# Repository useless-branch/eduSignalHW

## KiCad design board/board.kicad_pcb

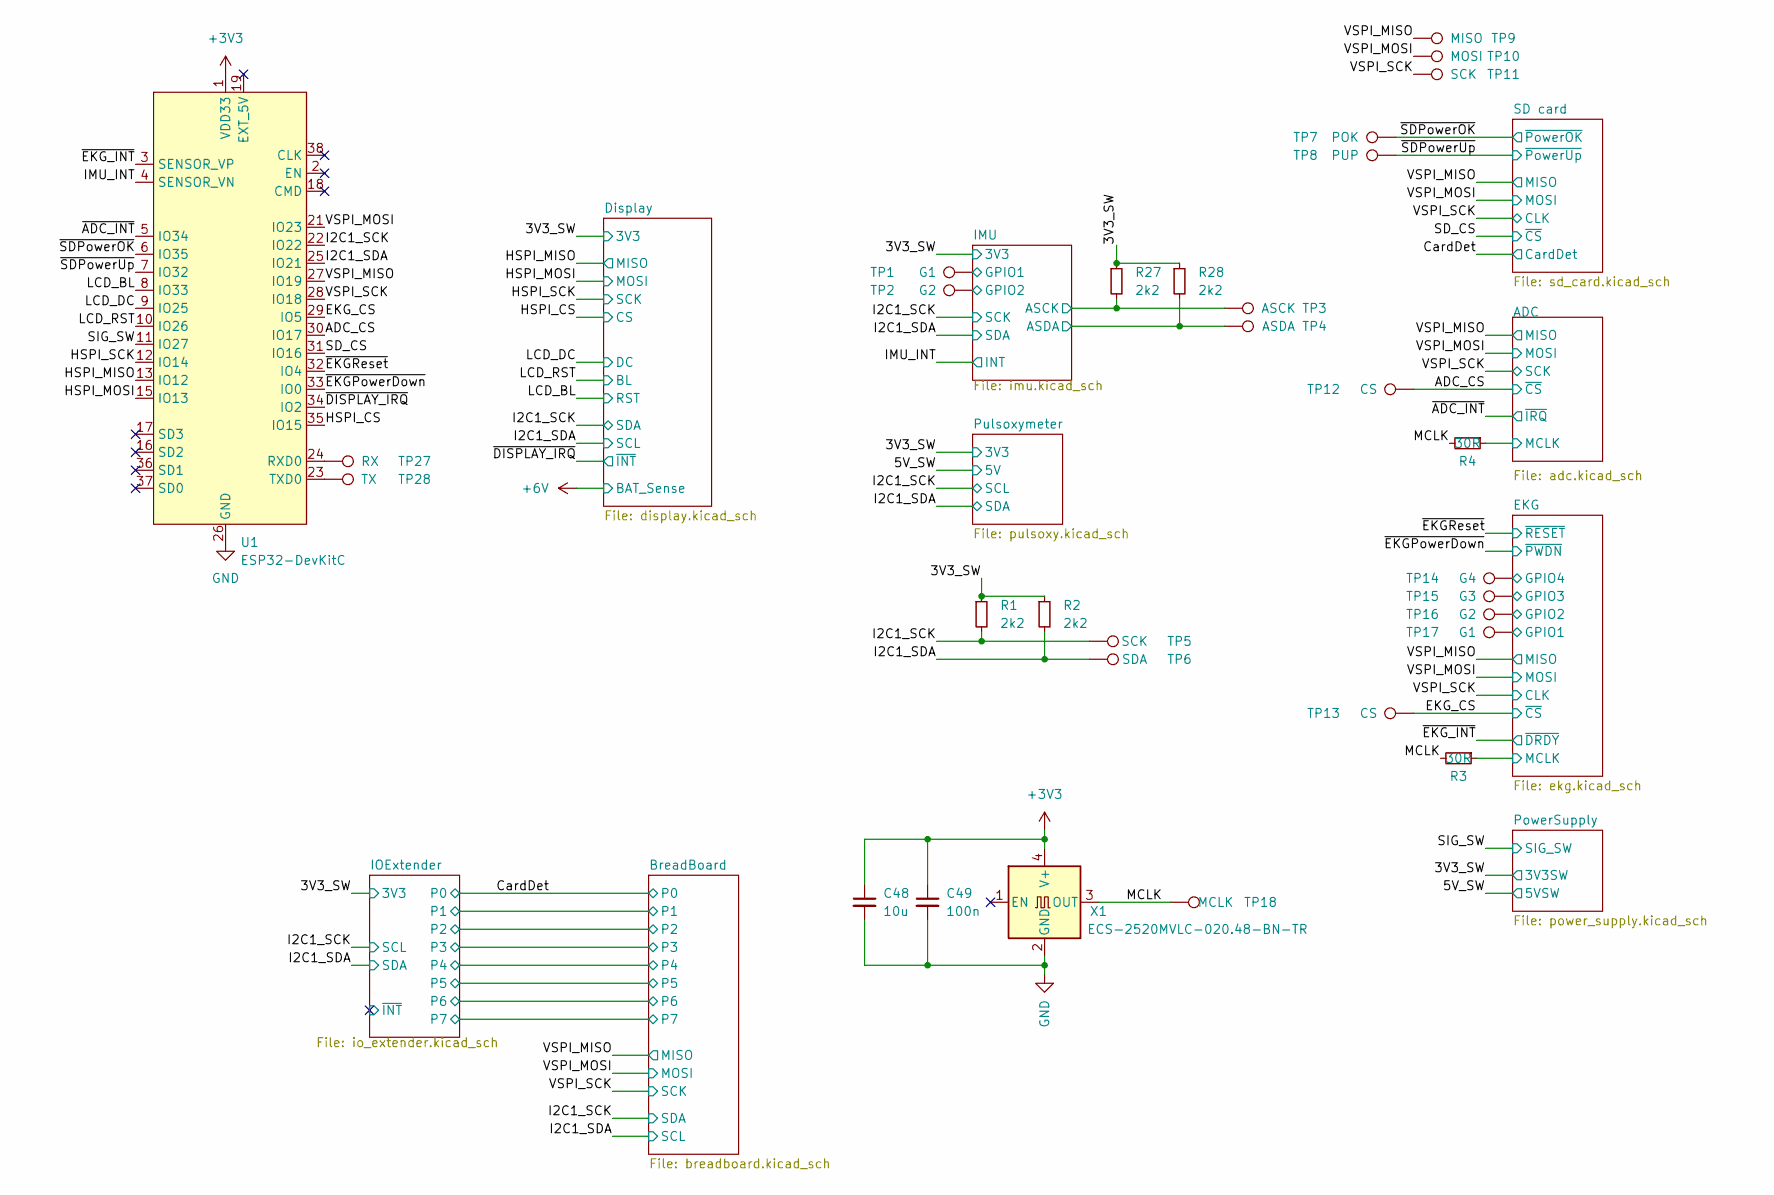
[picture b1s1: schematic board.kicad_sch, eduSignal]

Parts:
C48: 10u; C_0603_1608Metric
C49: 100n; C_0402_1005Metric
R1, R2, R27, R28: 2k2; R_0402_1005Metric
R3, R4: 30R; R_0402_1005Metric
TP1, TP17: G1; TestPoint_Pad_D1.0mm
TP2, TP16: G2; TestPoint_Pad_D1.0mm
TP3: ASCK; TestPoint_Pad_D1.0mm
TP4: ASDA; TestPoint_Pad_D1.0mm
TP5, TP11: SCK; TestPoint_Pad_D1.0mm
TP6: SDA; TestPoint_Pad_D1.0mm
TP7: POK; TestPoint_Pad_D1.0mm
TP8: PUP; TestPoint_Pad_D1.0mm
TP9: MISO; TestPoint_Pad_D1.0mm
TP10: MOSI; TestPoint_Pad_D1.0mm
TP12, TP13: CS; TestPoint_Pad_D1.0mm
TP14: G4; TestPoint_Pad_D1.0mm
TP15: G3; TestPoint_Pad_D1.0mm
TP18: MCLK; TestPoint_Pad_D1.0mm
TP27: RX; TestPoint_Pad_D1.0mm
TP28: TX; TestPoint_Pad_D1.0mm
U1: ESP32-DevKitC
X1: ECS-2520MVLC-020.48-BN-TR; Oscillator_SMD_EuroQuartz_XO32-4Pin_3.2x2.5mm

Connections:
+3V3: C48.1, C49.1, U1.1 (VDD33), X1.4 (V+); also elsewhere on the board
/3V3_SW: R1.1, R2.1, R27.1, R28.1; also elsewhere on the board
/ADC/MCLK: R4.1; also elsewhere on the board
/ADC_CS: TP12.1, U1.30 (IO17); also elsewhere on the board
/EKG/GPIO1: TP17.1; also elsewhere on the board
/EKG/GPIO2: TP16.1; also elsewhere on the board
/EKG/GPIO3: TP15.1; also elsewhere on the board
/EKG/GPIO4: TP14.1; also elsewhere on the board
/EKG/MCLK: R3.1; also elsewhere on the board
/EKG_CS: TP13.1, U1.29 (IO5); also elsewhere on the board
/HSPI_CS: U1.35 (IO15); also elsewhere on the board
/HSPI_MISO: U1.13 (IO12); also elsewhere on the board
/HSPI_MOSI: U1.15 (IO13); also elsewhere on the board
/HSPI_SCK: U1.12 (IO14); also elsewhere on the board
/I2C1_SCK: R1.2, TP5.1, U1.22 (IO22); also elsewhere on the board
/I2C1_SDA: R2.2, TP6.1, U1.25 (IO21); also elsewhere on the board
/IMU/ASCK: R27.2, TP3.1; also elsewhere on the board
/IMU/ASDA: R28.2, TP4.1; also elsewhere on the board
/IMU/GPIO1: TP1.1; also elsewhere on the board
/IMU/GPIO2: TP2.1; also elsewhere on the board
/IMU_INT: U1.4 (SENSOR_VN); also elsewhere on the board
/LCD_BL: U1.8 (IO33); also elsewhere on the board
/LCD_DC: U1.9 (IO25); also elsewhere on the board
/LCD_RST: U1.10 (IO26); also elsewhere on the board
/MCLK: R3.2, R4.2, TP18.1, X1.3 (OUT)
/SD_CS: U1.31 (IO16); also elsewhere on the board
/SIG_SW: U1.11 (IO27); also elsewhere on the board
/VSPI_MISO: TP9.1, U1.27 (IO19); also elsewhere on the board
/VSPI_MOSI: TP10.1, U1.21 (IO23); also elsewhere on the board
/VSPI_SCK: TP11.1, U1.28 (IO18); also elsewhere on the board
/~ADC_INT: U1.5 (IO34); also elsewhere on the board
/~DISPLAY_IRQ: U1.34 (IO2); also elsewhere on the board
/~EKGPowerDown: U1.33 (IO0); also elsewhere on the board
/~EKGReset: U1.32 (IO4); also elsewhere on the board
/~EKG_INT: U1.3 (SENSOR_VP); also elsewhere on the board
/~SDPowerOK: TP7.1, U1.6 (IO35); also elsewhere on the board
/~SDPowerUp: TP8.1, U1.7 (IO32); also elsewhere on the board
unnamed: TP27.1, U1.24 (RXD0)
unnamed: TP28.1, U1.23 (TXD0)

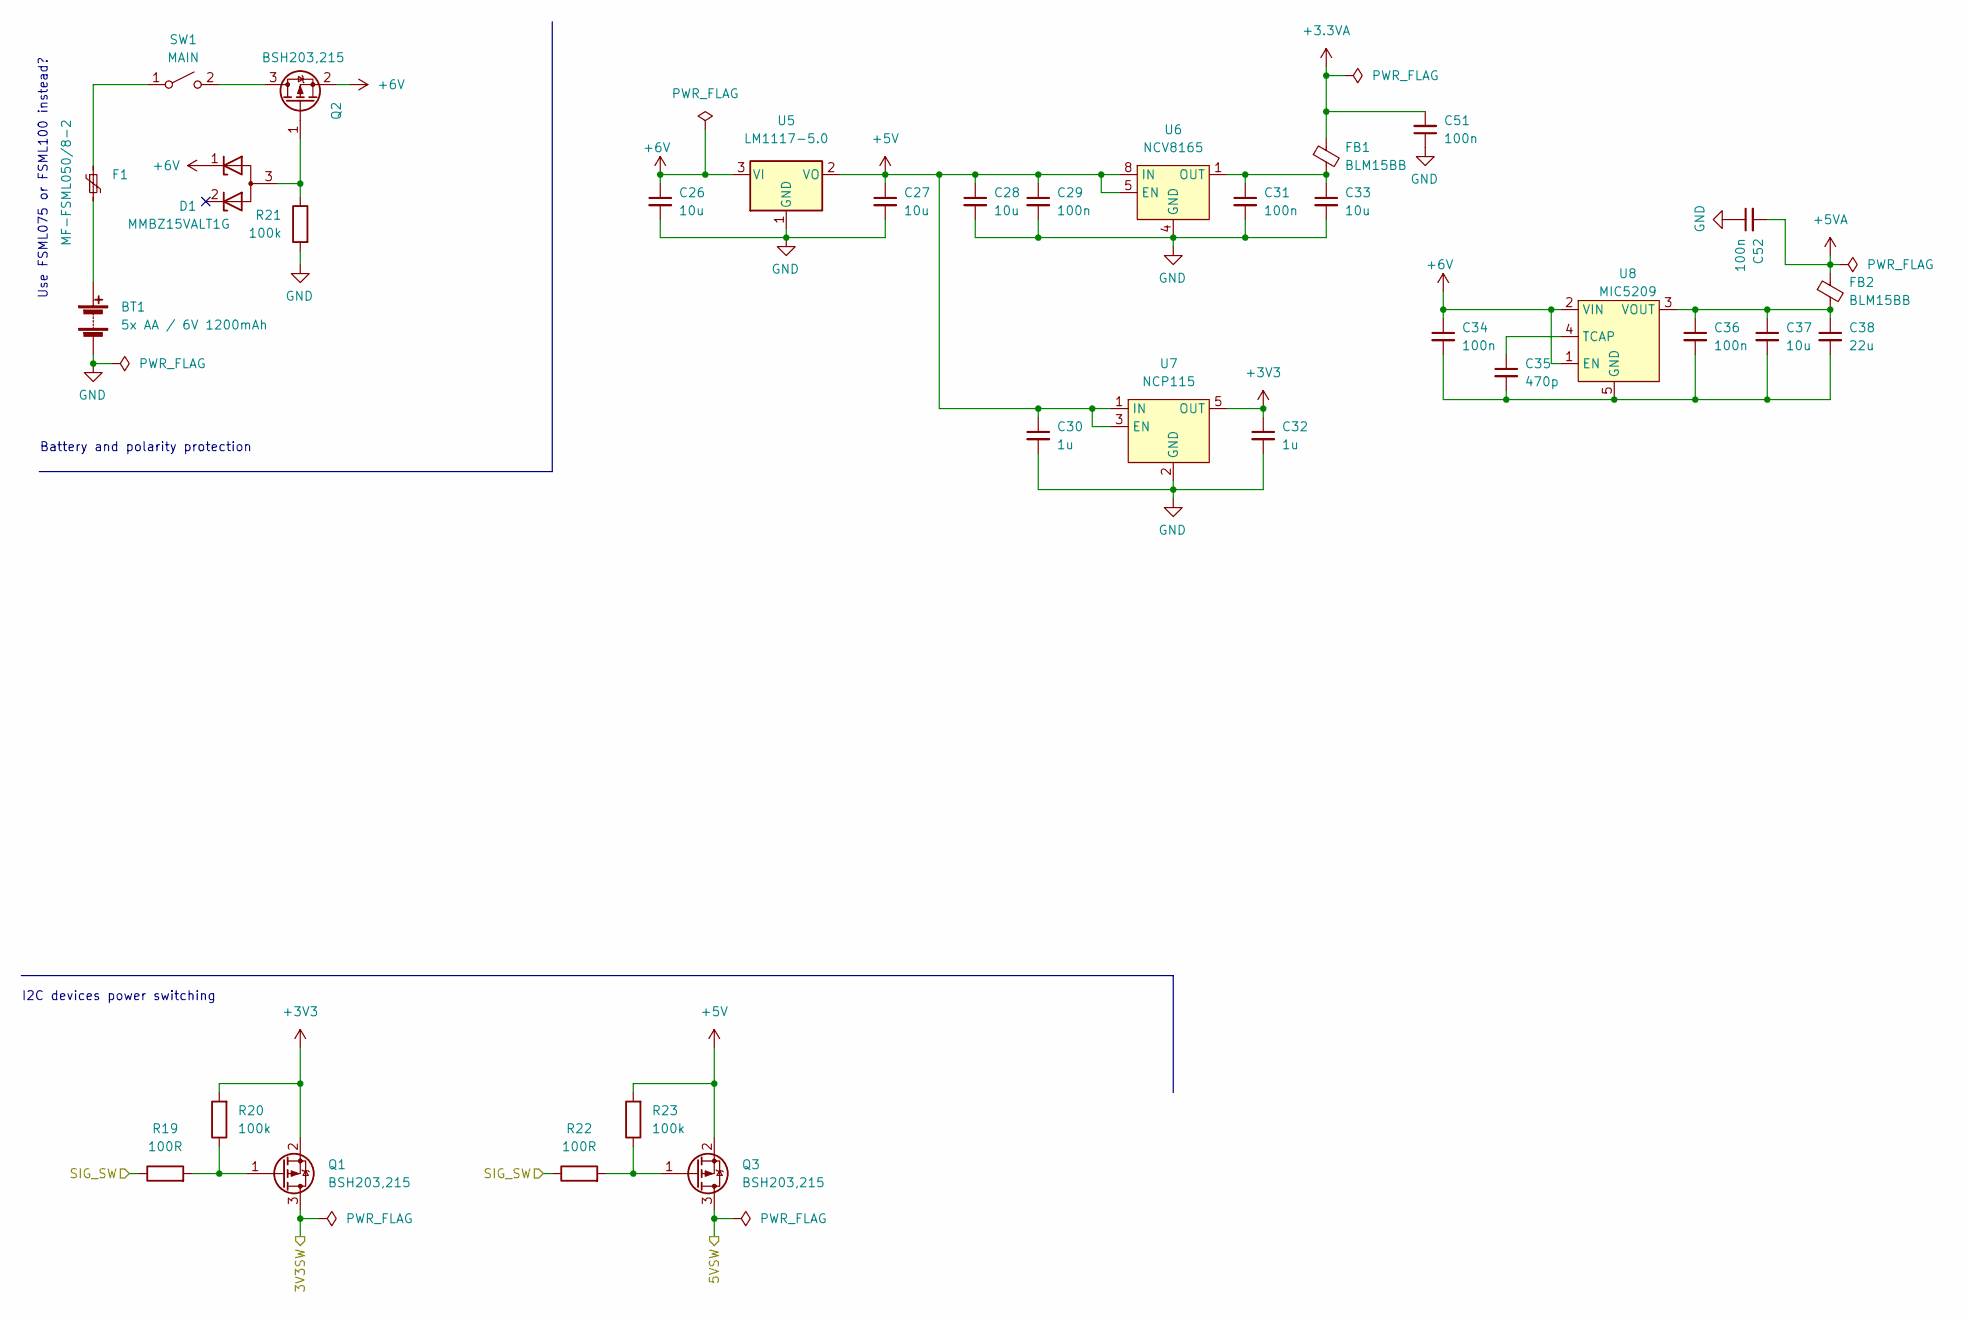
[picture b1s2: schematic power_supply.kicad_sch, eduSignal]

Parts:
BT1: 5x AA / 6V 1200mAh; PinHeader_1x02_P2.54mm_Vertical
C26, C27, C28, C33, C37: 10u; C_0603_1608Metric
C29, C31, C34, C36, C51, C52: 100n; C_0402_1005Metric
C30, C32: 1u; C_0603_1608Metric
C35: 470p; C_0402_1005Metric
C38: 22u; C_0805_2012Metric
D1: MMBZ15VALT1G; SOT-23; MOUSER_NO 863-SZMMBZ15VALT1G
F1: MF-FSML050/8-2; MF-FSML
FB1, FB2: BLM15BB; C_0402_1005Metric
Q1, Q3: BSH203,215; SOT-23; MOUSER_NO 78-SI2337DS-T1-BE3
Q2: BSH203,215; SOT-23; MOUSER_NO 771-BSH203215
R19, R22: 100R; R_0402_1005Metric; MOUSER_NO DO NOT ORDER
R20, R21, R23: 100k; R_0402_1005Metric; MOUSER_NO DO NOT ORDER
SW1: MAIN; PinHeader_1x02_P2.54mm_Vertical
U5: LM1117-5.0; SOT-223
U6: NCV8165; DFN-8-1EP_3x3mm_P0.65mm_EP1.7x2.05mm
U7: NCP115; TSOT-23-5
U8: MIC5209; SOICN-8LD

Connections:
+3.3VA: C51.2, FB1.1; also elsewhere on the board
+3V3: C32.1, Q1.2 (S), R20.2, U7.5 (OUT); also elsewhere on the board
+5V: C27.1, C28.1, C29.1, C30.1, Q3.2 (S), R23.2, U5.2 (VO), U5.4 (VO), U6.5 (EN), U6.8 (IN), U7.1 (IN), U7.3 (EN); also elsewhere on the board
+5VA: C52.2, FB2.1; also elsewhere on the board
+6V: C26.1, C34.1, D1.1 (K), Q2.2 (S), U5.3 (VI), U8.1 (EN), U8.2 (VIN); also elsewhere on the board
/3V3_SW: Q1.3 (D); also elsewhere on the board
/5V_SW: Q3.3 (D); also elsewhere on the board
/SIG_SW: R19.1, R22.1; also elsewhere on the board
unnamed: BT1.1 (+), F1.2
unnamed: C31.1, C33.1, FB1.2, U6.1 (OUT)
unnamed: C35.1, U8.4 (TCAP)
unnamed: C36.1, C37.1, C38.1, FB2.2, U8.3 (VOUT)
unnamed: D1.3 (A), Q2.1 (G), R21.1
unnamed: F1.1, SW1.1 (A)
unnamed: Q1.1 (G), R19.2, R20.1
unnamed: Q2.3 (D), SW1.2 (B)
unnamed: Q3.1 (G), R22.2, R23.1

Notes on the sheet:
I2C devices power switching
Battery and polarity protection
Use FSML075 or FSML100 instead?

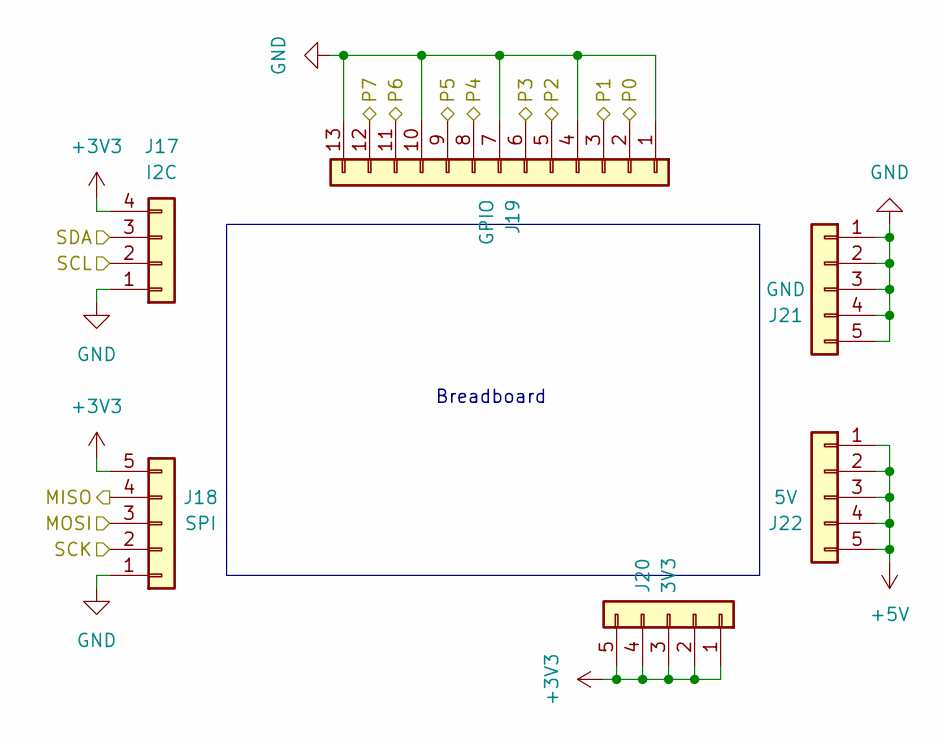
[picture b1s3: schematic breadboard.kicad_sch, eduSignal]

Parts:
J17: I2C; PinHeader_1x04_P2.54mm_Vertical
J18: SPI; PinHeader_1x05_P2.54mm_Vertical
J19: GPIO; PinHeader_1x13_P2.54mm_Vertical
J20: 3V3; PinHeader_1x05_P2.54mm_Vertical
J21: GND; PinHeader_1x05_P2.54mm_Vertical
J22: 5V; PinHeader_1x05_P2.54mm_Vertical

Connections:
+3V3: J17.4, J18.5, J20.1, J20.2, J20.3, J20.4, J20.5; also elsewhere on the board
+5V: J22.1, J22.2, J22.3, J22.4, J22.5; also elsewhere on the board
/BreadBoard/P1: J19.3; also elsewhere on the board
/BreadBoard/P2: J19.5; also elsewhere on the board
/BreadBoard/P3: J19.6; also elsewhere on the board
/BreadBoard/P4: J19.8; also elsewhere on the board
/BreadBoard/P5: J19.9; also elsewhere on the board
/BreadBoard/P6: J19.11; also elsewhere on the board
/BreadBoard/P7: J19.12; also elsewhere on the board
/CardDet: J19.2; also elsewhere on the board
/I2C1_SCK: J17.3; also elsewhere on the board
/I2C1_SDA: J17.2; also elsewhere on the board
/VSPI_MISO: J18.4; also elsewhere on the board
/VSPI_MOSI: J18.3; also elsewhere on the board
/VSPI_SCK: J18.2; also elsewhere on the board

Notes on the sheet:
Breadboard

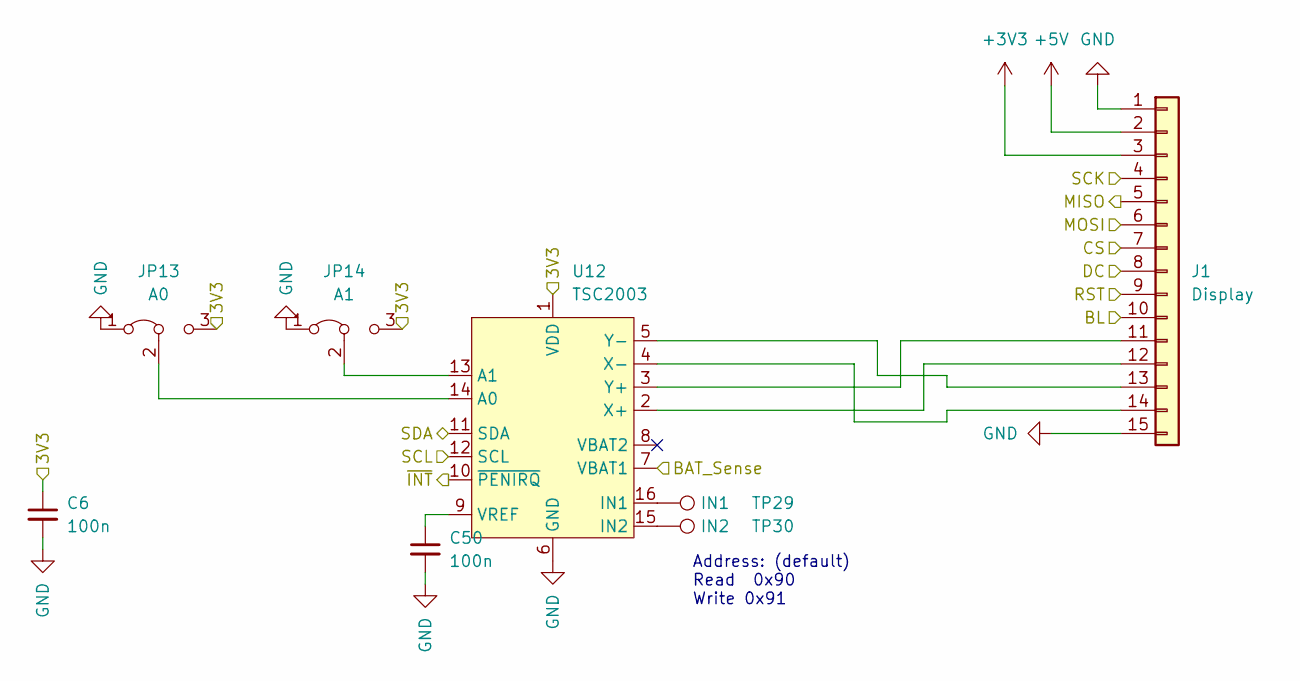
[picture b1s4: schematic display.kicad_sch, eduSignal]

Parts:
C6, C50: 100n; C_0402_1005Metric
J1: Display; PinHeader_1x15_P2.54mm_Vertical
JP13: A0; SolderJumper-3_P1.3mm_Bridged12_Pad1.0x1.5mm
JP14: A1; SolderJumper-3_P1.3mm_Bridged12_Pad1.0x1.5mm
TP29: IN1; TestPoint_Pad_D1.0mm
TP30: IN2; TestPoint_Pad_D1.0mm
U12: TSC2003; TSSOP-16_4.4x5mm_P0.65mm_EP3x3mm

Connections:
+3V3: J1.3; also elsewhere on the board
+5V: J1.2; also elsewhere on the board
+6V: U12.7 (VBAT1); also elsewhere on the board
/3V3_SW: C6.1, JP13.3 (B), JP14.3 (B), U12.1 (VDD); also elsewhere on the board
/HSPI_CS: J1.7; also elsewhere on the board
/HSPI_MISO: J1.5; also elsewhere on the board
/HSPI_MOSI: J1.6; also elsewhere on the board
/HSPI_SCK: J1.4; also elsewhere on the board
/I2C1_SCK: U12.11 (SDA); also elsewhere on the board
/I2C1_SDA: U12.12 (SCL); also elsewhere on the board
/LCD_BL: J1.9; also elsewhere on the board
/LCD_DC: J1.8; also elsewhere on the board
/LCD_RST: J1.10; also elsewhere on the board
/~DISPLAY_IRQ: U12.10 (~PENIRQ); also elsewhere on the board
unnamed: C50.1, U12.9 (VREF)
unnamed: J1.11, U12.3 (Y+)
unnamed: J1.12, U12.2 (X+)
unnamed: J1.13, U12.5 (Y-)
unnamed: J1.14, U12.4 (X-)
unnamed: JP13.2 (C), U12.14 (A0)
unnamed: JP14.2 (C), U12.13 (A1)
unnamed: TP29.1, U12.16 (IN1)
unnamed: TP30.1, U12.15 (IN2)

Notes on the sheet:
Address: (default) Read 0x90 Write 0x91

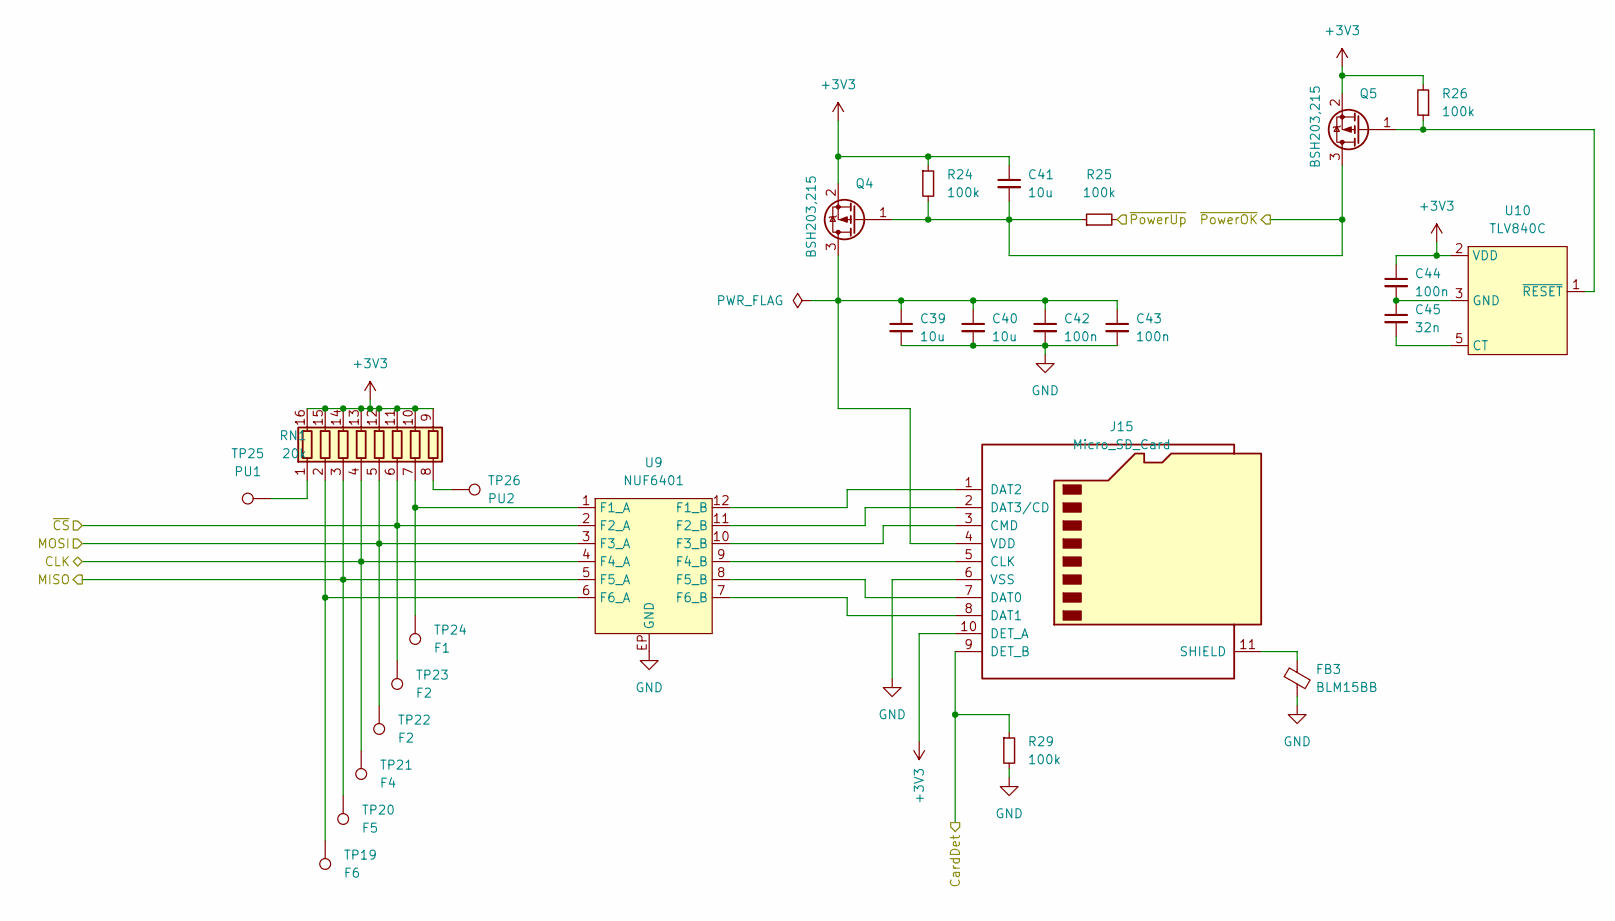
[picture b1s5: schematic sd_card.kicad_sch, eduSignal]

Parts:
C39, C40, C41: 10u; C_0603_1608Metric
C42, C43, C44: 100n; C_0402_1005Metric
C45: 32n; C_0402_1005Metric
FB3: BLM15BB; C_0402_1005Metric
J15: Micro_SD_Card; GCT MEM2061
Q4, Q5: BSH203,215; SOT-23; MOUSER_NO 771-BSH203215
R24, R25, R26, R29: 100k; R_0402_1005Metric
RN1: 20k; R_Array_Convex_8x0602
TP19: F6; TestPoint_Pad_D1.0mm
TP20: F5; TestPoint_Pad_D1.0mm
TP21: F4; TestPoint_Pad_D1.0mm
TP22, TP23: F2; TestPoint_Pad_D1.0mm
TP24: F1; TestPoint_Pad_D1.0mm
TP25: PU1; TestPoint_Pad_D1.0mm
TP26: PU2; TestPoint_Pad_D1.0mm
U9: NUF6401
U10: TLV840C; SOT-23-5

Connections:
+3V3: C41.1, C44.1, J15.10 (DET_A), Q4.2 (S), Q5.2 (S), R24.1, R26.2, RN1.9 (R8.2), RN1.10 (R7.2), RN1.11 (R6.2), RN1.12 (R5.2), RN1.13 (R4.2), RN1.14 (R3.2), RN1.15 (R2.2), RN1.16 (R1.2), U10.2 (VDD); also elsewhere on the board
/CardDet: J15.9 (DET_B), R29.1; also elsewhere on the board
/SD_CS: RN1.6 (R6.1), TP23.1, U9.2 (F2_A); also elsewhere on the board
/VSPI_MISO: RN1.3 (R3.1), TP20.1, U9.5 (F5_A); also elsewhere on the board
/VSPI_MOSI: RN1.5 (R5.1), TP22.1, U9.3 (F3_A); also elsewhere on the board
/VSPI_SCK: RN1.4 (R4.1), TP21.1, U9.4 (F4_A); also elsewhere on the board
/~SDPowerOK: C41.2, Q4.1 (G), Q5.3 (D), R24.2, R25.1; also elsewhere on the board
/~SDPowerUp: R25.2; also elsewhere on the board
unnamed: C39.1, C40.1, C42.1, C43.1, J15.4 (VDD), Q4.3 (D)
unnamed: C44.2, C45.1, U10.3 (GND)
unnamed: C45.2, U10.5 (CT)
unnamed: FB3.1, J15.11 (SHIELD)
unnamed: J15.1 (DAT2), U9.12 (F1_B)
unnamed: J15.2 (DAT3/CD), U9.11 (F2_B)
unnamed: J15.3 (CMD), U9.10 (F3_B)
unnamed: J15.5 (CLK), U9.9 (F4_B)
unnamed: J15.7 (DAT0), U9.8 (F5_B)
unnamed: J15.8 (DAT1), U9.7 (F6_B)
unnamed: Q5.1 (G), R26.1, U10.1 (~RESET)
unnamed: RN1.1 (R1.1), TP25.1
unnamed: RN1.2 (R2.1), TP19.1, U9.6 (F6_A)
unnamed: RN1.7 (R7.1), TP24.1, U9.1 (F1_A)
unnamed: RN1.8 (R8.1), TP26.1

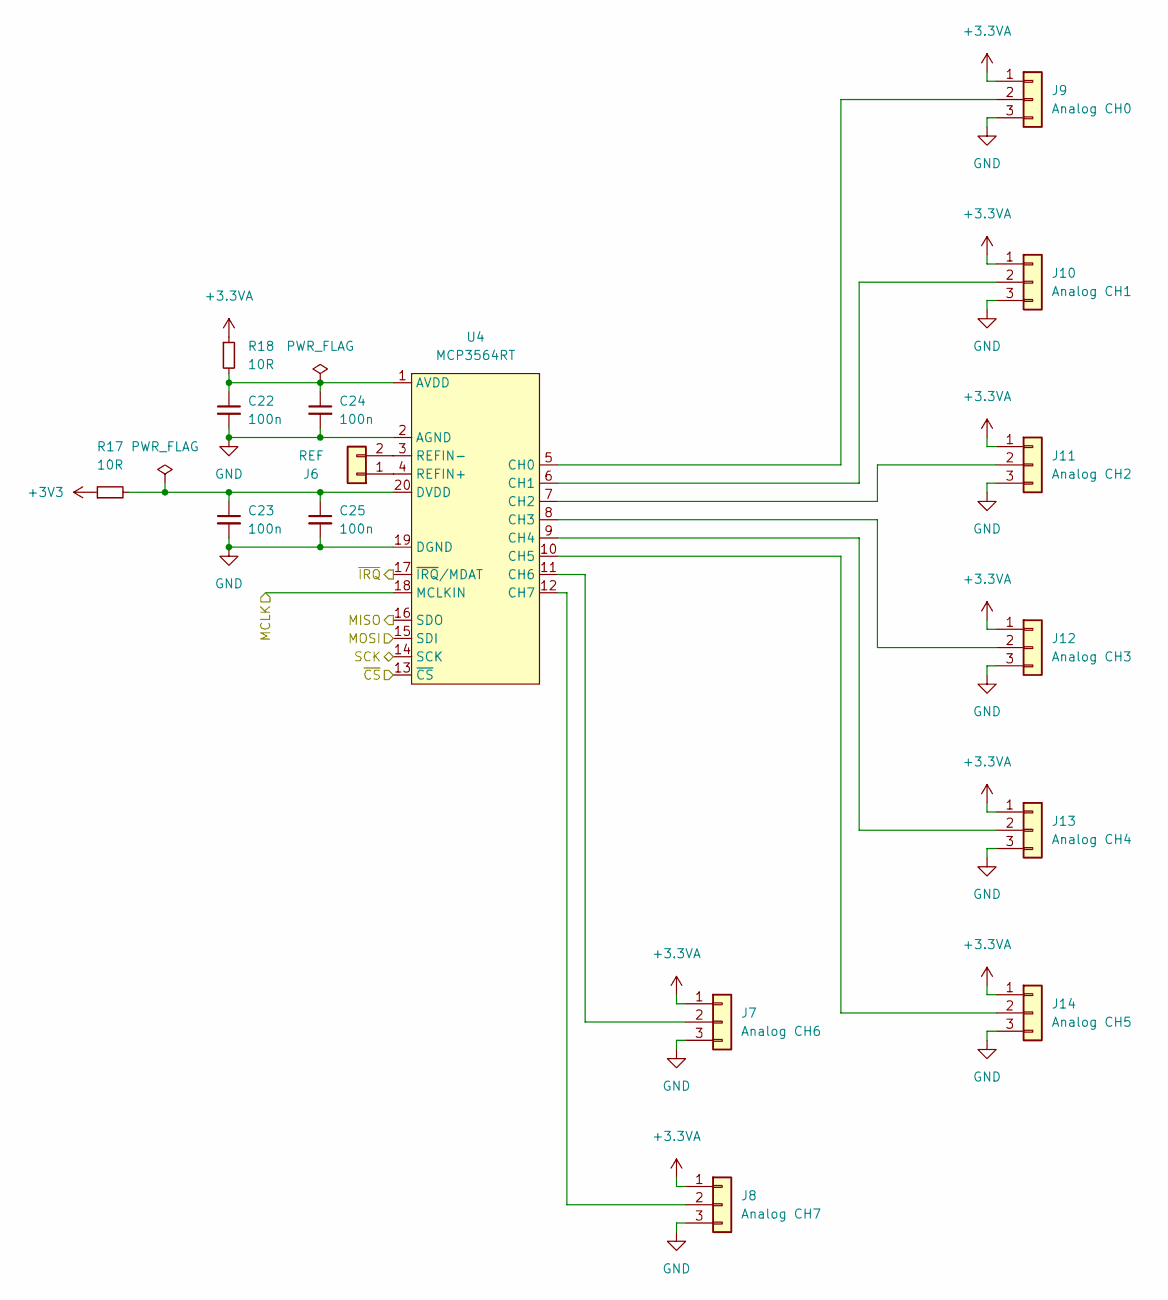
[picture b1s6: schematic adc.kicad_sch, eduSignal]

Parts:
C22, C23, C24, C25: 100n; C_0402_1005Metric
J6: REF; PinHeader_1x02_P2.54mm_Vertical
J7: Analog CH6; PinHeader_1x03_P2.54mm_Vertical
J8: Analog CH7; PinHeader_1x03_P2.54mm_Vertical
J9: Analog CH0; PinHeader_1x03_P2.54mm_Vertical
J10: Analog CH1; PinHeader_1x03_P2.54mm_Vertical
J11: Analog CH2; PinHeader_1x03_P2.54mm_Vertical
J12: Analog CH3; PinHeader_1x03_P2.54mm_Vertical
J13: Analog CH4; PinHeader_1x03_P2.54mm_Vertical
J14: Analog CH5; PinHeader_1x03_P2.54mm_Vertical
R17, R18: 10R; R_0402_1005Metric
U4: MCP3564RT; HTSSOP-20-1EP_4.4x6.5mm_P0.65mm_3.4x6.5mm_Mask2.75x3.43mm

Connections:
+3.3VA: J7.1, J8.1, J9.1, J10.1, J11.1, J12.1, J13.1, J14.1, R18.1; also elsewhere on the board
+3V3: R17.1; also elsewhere on the board
/ADC/MCLK: U4.18 (MCLKIN); also elsewhere on the board
/ADC_CS: U4.13 (~CS); also elsewhere on the board
/VSPI_MISO: U4.16 (SDO); also elsewhere on the board
/VSPI_MOSI: U4.15 (SDI); also elsewhere on the board
/VSPI_SCK: U4.14 (SCK); also elsewhere on the board
/~ADC_INT: U4.17 (~IRQ/MDAT); also elsewhere on the board
unnamed: C22.1, C24.1, R18.2, U4.1 (AVDD)
unnamed: C23.1, C25.1, R17.2, U4.20 (DVDD)
unnamed: J6.1, U4.4 (REFIN+)
unnamed: J6.2, U4.3 (REFIN-)
unnamed: J7.2, U4.11 (CH6)
unnamed: J8.2, U4.12 (CH7)
unnamed: J9.2, U4.5 (CH0)
unnamed: J10.2, U4.6 (CH1)
unnamed: J11.2, U4.7 (CH2)
unnamed: J12.2, U4.8 (CH3)
unnamed: J13.2, U4.9 (CH4)
unnamed: J14.2, U4.10 (CH5)

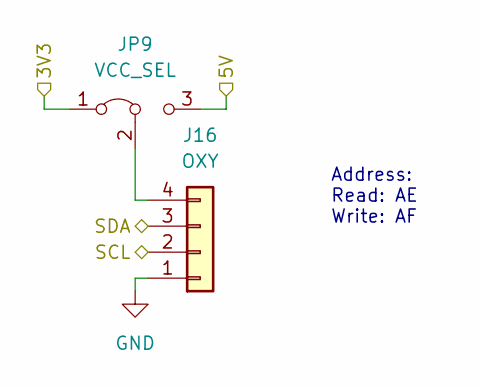
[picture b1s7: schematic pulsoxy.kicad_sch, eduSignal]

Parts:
J16: OXY; PinHeader_1x04_P2.54mm_Vertical
JP9: VCC_SEL; SolderJumper-3_P1.3mm_Bridged12_Pad1.0x1.5mm

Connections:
/3V3_SW: JP9.1 (A); also elsewhere on the board
/5V_SW: JP9.3 (B); also elsewhere on the board
/I2C1_SCK: J16.2; also elsewhere on the board
/I2C1_SDA: J16.3; also elsewhere on the board
unnamed: J16.4, JP9.2 (C)

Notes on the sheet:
Address: Read: AE Write: AF

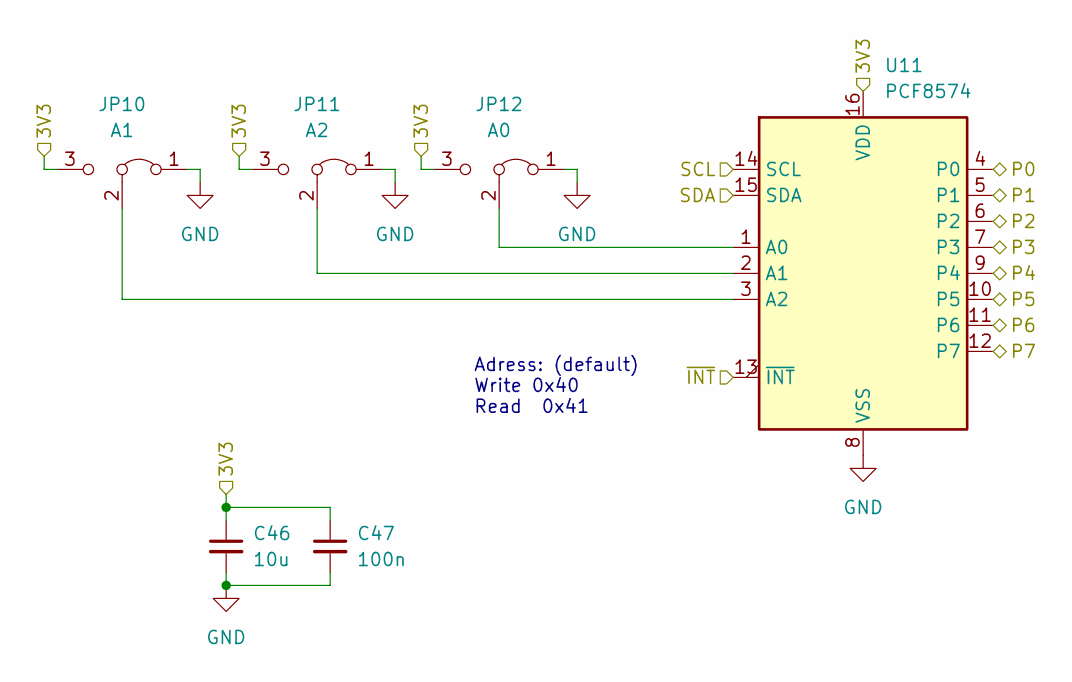
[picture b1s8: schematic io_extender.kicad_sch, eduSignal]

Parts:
C46: 10u; C_0603_1608Metric
C47: 100n; C_0402_1005Metric
JP10: A1; SolderJumper-3_P1.3mm_Bridged12_Pad1.0x1.5mm
JP11: A2; SolderJumper-3_P1.3mm_Bridged12_Pad1.0x1.5mm
JP12: A0; SolderJumper-3_P1.3mm_Bridged12_Pad1.0x1.5mm
U11: PCF8574; SOIC-16W_7.5x10.3mm_P1.27mm

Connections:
/3V3_SW: C46.1, C47.1, JP10.3 (B), JP11.3 (B), JP12.3 (B), U11.16 (VDD); also elsewhere on the board
/BreadBoard/P1: U11.5 (P1); also elsewhere on the board
/BreadBoard/P2: U11.6 (P2); also elsewhere on the board
/BreadBoard/P3: U11.7 (P3); also elsewhere on the board
/BreadBoard/P4: U11.9 (P4); also elsewhere on the board
/BreadBoard/P5: U11.10 (P5); also elsewhere on the board
/BreadBoard/P6: U11.11 (P6); also elsewhere on the board
/BreadBoard/P7: U11.12 (P7); also elsewhere on the board
/CardDet: U11.4 (P0); also elsewhere on the board
/I2C1_SCK: U11.14 (SCL); also elsewhere on the board
/I2C1_SDA: U11.15 (SDA); also elsewhere on the board
/IOExtender/~INT: U11.13 (~INT)
unnamed: JP10.2 (C), U11.3 (A2)
unnamed: JP11.2 (C), U11.2 (A1)
unnamed: JP12.2 (C), U11.1 (A0)

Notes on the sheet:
Adress: (default) Write 0x40 Read 0x41

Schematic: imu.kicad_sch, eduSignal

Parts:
C18, C20: 100n; C_0402_1005Metric
C19: 1u; C_0603_1608Metric
C21: 470n; C_0402_1005Metric
JP8: AddrSelect; SolderJumper-3_P1.3mm_Bridged12_Pad1.0x1.5mm
U3: BHI160

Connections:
/3V3_SW: C18.1, C19.1, C20.1, JP8.3 (B), U3.8 (VDDIO), U3.13 (VDD); also elsewhere on the board
/I2C1_SCK: U3.23 (SCK); also elsewhere on the board
/I2C1_SDA: U3.24 (SDA); also elsewhere on the board
/IMU/ASCK: U3.7 (ASCK); also elsewhere on the board
/IMU/ASDA: U3.21 (ASDA); also elsewhere on the board
/IMU/GPIO1: U3.3 (GPIO1); also elsewhere on the board
/IMU/GPIO2: U3.11 (GPIO2); also elsewhere on the board
/IMU_INT: U3.12 (INT); also elsewhere on the board
unnamed: C21.1, U3.10 (VREG)
unnamed: JP8.2 (C), U3.9 (SA_GPIO7)

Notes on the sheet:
Keep layout recommendation in mind
Low: Address 0x28 (default) High: Address 0x29

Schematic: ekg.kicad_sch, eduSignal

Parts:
C1: C_{F}; C_0603_1608Metric_Pad1.08x0.95mm_HandSolder
C2: 10u; C_0603_1608Metric
C3, C7, C13: 100n; C_0402_1005Metric
C4: 100u; C_1206_3216Metric
C5, C8, C9, C10, C11, C12: 1u; C_0603_1608Metric
C14, C15, C16, C17: C_{Filt}; C_0603_1608Metric_Pad1.08x0.95mm_HandSolder
J2: BIAS; PinHeader_1x05_P2.54mm_Vertical
J3: SRB; PinHeader_1x02_P2.54mm_Vertical
JP1: FILTER OUT; PinHeader_1x03_P2.54mm_Vertical
JP2: BIASINV SEL; PinHeader_1x03_P2.54mm_Vertical
JP3: BIASOUT SEL; PinHeader_1x03_P2.54mm_Vertical
R5: R_{P}; R_0603_1608Metric_Pad0.98x0.95mm_HandSolder
R6: R_{F}; R_0603_1608Metric_Pad0.98x0.95mm_HandSolder
R7, R8: 10k; R_0402_1005Metric
R9, R10, R11, R12, R13, R14, R15, R16: R_{Filt}; R_0603_1608Metric_Pad0.98x0.95mm_HandSolder
U2: ADS1299-x; TQFP-64_10x10mm_P0.5mm

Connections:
+3V3: C10.1, C13.1, R7.1, U2.48 (DVDD), U2.50 (DVDD); also elsewhere on the board
+5VA: C11.1, C12.2, U2.1 (IN8N), U2.2 (IN8P), U2.3 (IN7N), U2.4 (IN7P), U2.5 (IN6N), U2.6 (IN6P), U2.7 (IN5N), U2.8 (IN5P), U2.19 (AVDD), U2.21 (AVDD), U2.22 (AVDD), U2.54 (AVDD1), U2.56 (AVDD), U2.59 (AVDD); also elsewhere on the board
/EKG/EEGMux/BIAS: JP1.2 (C); also elsewhere on the board
/EKG/EEGMux/IN1N: R10.2; also elsewhere on the board
/EKG/EEGMux/IN1P: R9.2; also elsewhere on the board
/EKG/EEGMux/IN2N: R12.2; also elsewhere on the board
/EKG/EEGMux/IN2P: R11.2; also elsewhere on the board
/EKG/EEGMux/IN3N: R14.2; also elsewhere on the board
/EKG/EEGMux/IN3P: R13.2; also elsewhere on the board
/EKG/EEGMux/IN4N: R16.2; also elsewhere on the board
/EKG/EEGMux/IN4P: R15.2; also elsewhere on the board
/EKG/GPIO1: U2.42 (GPIO1); also elsewhere on the board
/EKG/GPIO2: U2.44 (GPIO2); also elsewhere on the board
/EKG/GPIO3: U2.45 (GPIO3); also elsewhere on the board
/EKG/GPIO4: U2.46 (GPIO4); also elsewhere on the board
/EKG/MCLK: U2.37 (CLK); also elsewhere on the board
/EKG_CS: U2.39 (~CS); also elsewhere on the board
/VSPI_MISO: U2.43 (DOUT); also elsewhere on the board
/VSPI_MOSI: U2.34 (DIN); also elsewhere on the board
/VSPI_SCK: U2.40 (SCLK); also elsewhere on the board
/~EKGPowerDown: U2.35 (~PWDN); also elsewhere on the board
/~EKGReset: U2.36 (~RESET); also elsewhere on the board
/~EKG_INT: R7.2, U2.47 (~DRDY); also elsewhere on the board
unnamed: C1.1, JP2.1 (A), R6.1
unnamed: C1.2, JP3.1 (A), R5.2, R6.2
unnamed: C2.1, C3.1, U2.24 (VREFP)
unnamed: C4.1, U2.28 (VCAP1)
unnamed: C5.1, U2.30 (VCAP2)
unnamed: C7.1, C8.1, U2.55 (VCAP3)
unnamed: C9.1, U2.26 (VCAP4)
unnamed: C14.1, R9.1, U2.16 (IN1P)
unnamed: C14.2, R10.1, U2.15 (IN1N)
unnamed: C15.1, R11.1, U2.14 (IN2P)
unnamed: C15.2, R12.1, U2.13 (IN2N)
unnamed: C16.1, R13.1, U2.12 (IN3P)
unnamed: C16.2, R14.1, U2.11 (IN3N)
unnamed: C17.1, R15.1, U2.10 (IN4P)
unnamed: C17.2, R16.1, U2.9 (IN4N)
unnamed: J2.1, U2.62 (BIASIN)
unnamed: J2.2, JP2.3 (B)
unnamed: J2.3, JP3.3 (B)
unnamed: J2.4, U2.60 (BIASREF)
unnamed: J2.5, JP1.3 (B)
unnamed: J3.1, U2.17 (SRB1)
unnamed: J3.2, U2.18 (SRB2)
unnamed: JP1.1 (A), R5.1
unnamed: JP2.2 (C), U2.61 (BIASINV)
unnamed: JP3.2 (C), U2.63 (BIASOUT)
unnamed: R8.2, U2.52 (CLKSEL)

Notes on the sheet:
Jumper to include Filter

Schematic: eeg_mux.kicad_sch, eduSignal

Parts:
J4: EEG Out; PinHeader_1x09_P2.54mm_Vertical
J5: Device Electrodes; PinHeader_1x06_P2.54mm_Vertical
JP4: IN1N_SEL; PinHeader_1x03_P2.54mm_Vertical
JP5: IN2N_SEL; PinHeader_1x03_P2.54mm_Vertical
JP6: IN3N_SEL; PinHeader_1x03_P2.54mm_Vertical
JP7: IN4N_SEL; PinHeader_1x03_P2.54mm_Vertical

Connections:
/EKG/EEGMux/BIAS: J4.9, J5.6; also elsewhere on the board
/EKG/EEGMux/IN1N: JP4.2 (C); also elsewhere on the board
/EKG/EEGMux/IN1N_OUT: J4.2, JP4.1 (A)
/EKG/EEGMux/IN1P: J4.1, J5.1; also elsewhere on the board
/EKG/EEGMux/IN2N: JP5.2 (C); also elsewhere on the board
/EKG/EEGMux/IN2N_OUT: J4.4, JP5.1 (A)
/EKG/EEGMux/IN2P: J4.3, J5.2; also elsewhere on the board
/EKG/EEGMux/IN3N: JP6.2 (C); also elsewhere on the board
/EKG/EEGMux/IN3N_OUT: J4.6, JP6.1 (A)
/EKG/EEGMux/IN3P: J4.5, J5.3; also elsewhere on the board
/EKG/EEGMux/IN4N: JP7.2 (C); also elsewhere on the board
/EKG/EEGMux/IN4N_OUT: J4.8, JP7.1 (A)
/EKG/EEGMux/IN4P: J4.7, J5.4; also elsewhere on the board
/EKG/EEGMux/NCOMM: J5.5, JP4.3 (B), JP5.3 (B), JP6.3 (B), JP7.3 (B)

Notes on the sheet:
NCOMM Selector lets you choose between individual negative output electrodes or one single common output
To connect device with the internal electrodes connect IN1N and IN2N with the common electrode. Other channels are reserved for further use!

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
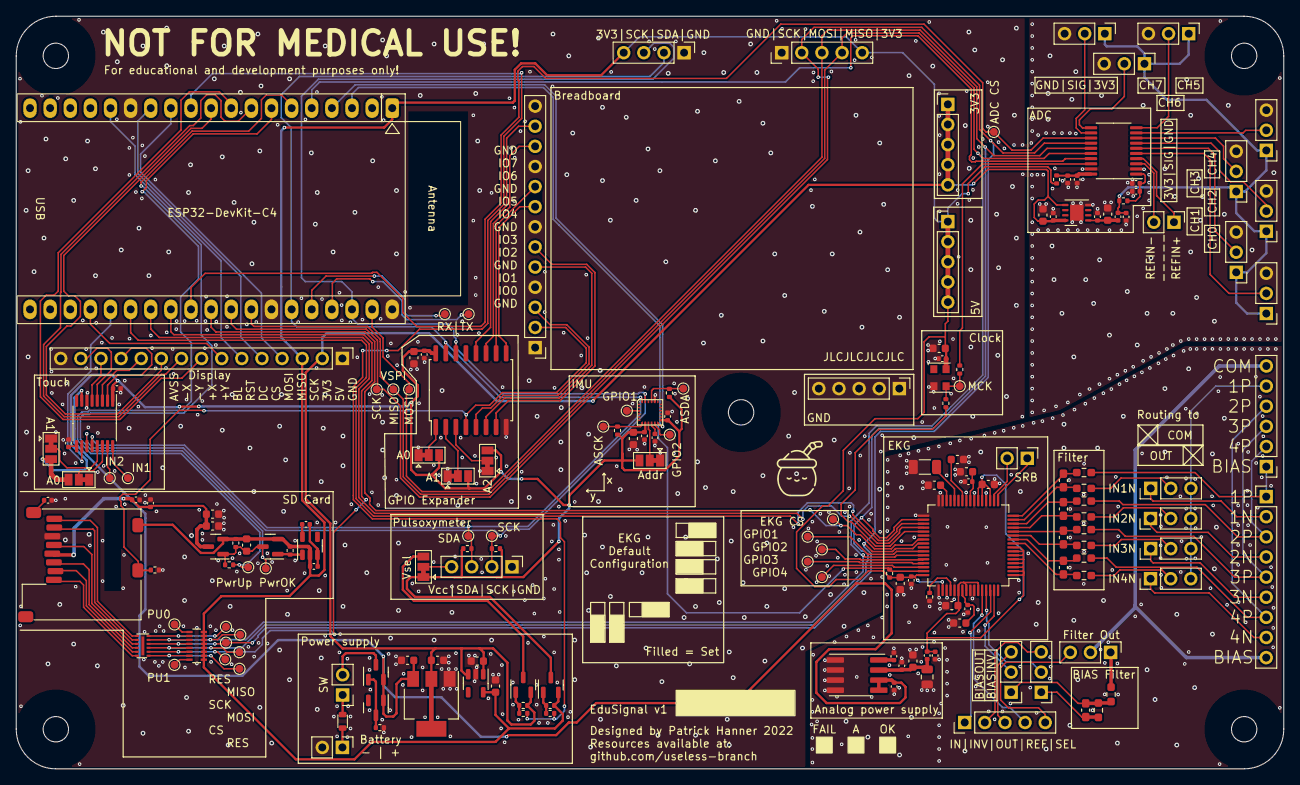
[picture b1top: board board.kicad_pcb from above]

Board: 4 copper layers, 160.0 x 95.0 mm, 178 parts (0 on the bottom side), 144 nets.

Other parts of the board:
H1, H2, H3, H3#2, H5: MountingHole; MountingHole_3.2mm_M3_no_Mask

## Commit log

2022-05-23 added ekg chip
2022-05-30 added filter and imu
2022-06-02 updated hw project
2022-06-07 updated schematic
2022-06-20 added SD card and pulsoxy
2022-06-22 updated schematic after review
2022-06-23 added io expander
2022-06-23 updated after meeting
2022-06-25 ERC run
2022-06-27 added fuse and capacitor to schematic
2022-06-27 added footprints to symbols and started layout
2022-06-30 WIP pushed for meeting
2022-06-30 updated 3d models
2022-07-07 redesigned board partially
2022-07-08 finished layout for review
2022-07-11 did some minor changes
2022-07-13 worked feedback into layout
2022-07-14 did some minor stuff
2022-07-16 worked feedback into layout with dp
2022-07-18 updated gerber data
2022-09-07 fixed errors in schematic
2022-10-24 Updated board
